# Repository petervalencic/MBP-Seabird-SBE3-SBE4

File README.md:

# Arduino Seabird SBE3 SBE4 

The project contains C/C++ code for Ardiuno Uno and a shield (Eagle project) for SBE-3 and SBE-4 

# SBE 3
Intended primarily for use on moored and fixed-site temperature measuring systems, the SBE 3S can also be used as a component in custom systems or for high-accuracy industrial and environmental temperature monitoring applications. The low noise characteristics of the SBE 3S allow the use of hybrid frequency measuring techniques to obtain rapid sampling with very high resolution; 40 μ°C resolution can be readily obtained at a 6 Hz sampling rate.

CALIBRATION EQUATION

The calibration yields four coefficients (g, h, i, j) that are used in the following equation (Bennett, 1972):

T [°C] = [1 / (g + hln(fo/f) + iln²(fo/f) + jln³(fo/f) )] - 273.15

where T is temperature [°C], ln is natural log function, and f is SBE 3S output frequency [Hz]. Note that fo, an arbitrary scaling term used for purposes of computational efficiency, was historically chosen as the lowest sensor frequency generated during calibration. For calibration results expressed in terms of ITS-90 temperatures, fo is set to 1000. Calibration fit residuals are typically less than 0.0001 °C.

Example Calibration Data (sensor serial number 2213, 30 May 1996):
g = 4.28793855e-03     h = 6.25807786e-04     i = 2.19368239e-05     j = 1.84262924e-06     f0 = 1000.000

# SBE 4
The SBE 4 conductivity sensor is a modular, self-contained instrument that measures conductivity from 0 to 7 S/m, covering the full range of lake and oceanic applications. The sensor has electrically isolated power circuits and optically coupled outputs to eliminate any possibility of noise and corrosion caused by ground loops. Interfacing is also simplified by the square-wave variable frequency output signal (nominally 2.5 to 7.5 kHz, corresponding to 0 to 7 S/m). The sensor offers improved temperature compensation, smaller fit residuals, and faster turn-on stabilization times.

Because of the SBE 4’s low noise characteristics, hybrid frequency measuring techniques (used in Sea-Bird’s CTD instruments) provide rapid sampling with very high temporal and spatial resolution.

CALIBRATION EQUATION

A least-squares fitting technique (including a zero conductivity point in air) yields calibration coefficients for use in the following equation:

Conductivity [S/m] = ( g + hf 2 + if 3+ jf 4 ) / 10 (1 + dt + ep)

where f is instrument frequency [kHz], t is temperature [°C], p is pressure [decibars], and d is thermal coefficient of expansion (3.25 x 10 -06) and e is bulk compressibility (-9.57 x 10 -08) of the borosilicate cell. The resulting coefficients g, h, i, and j are listed on the calibration certificate. Residuals are typically less than 0.0002 S/m.

Example Calibration Data (sensor serial number 2020, 30 May 1997)

Practical Salinity Scale 1978: C(35,15,0) = 4.2914 [S/m]

g = -1.05697877e+01    h = 1.42707291e+00    i = -4.32023820e-03    j = 4.53455585e-04

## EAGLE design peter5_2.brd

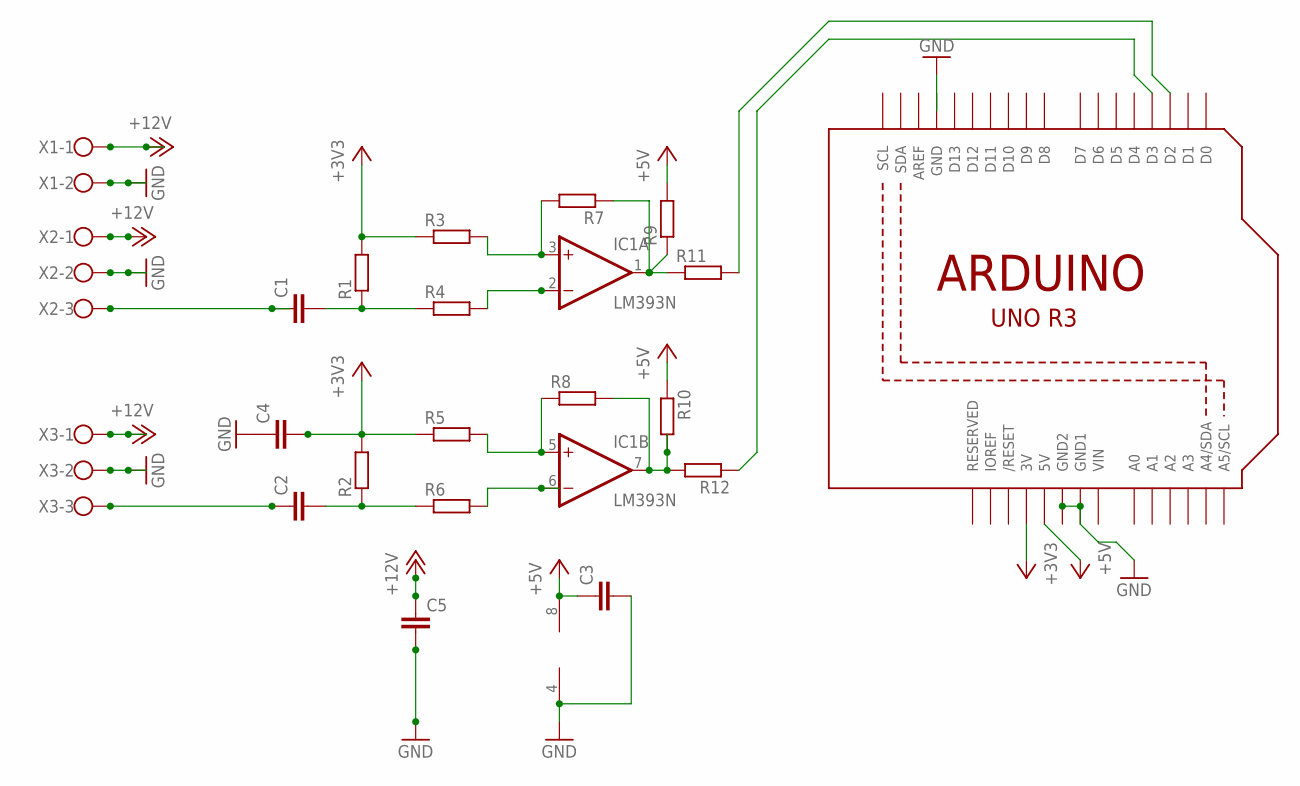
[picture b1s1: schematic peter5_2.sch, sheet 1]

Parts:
C1, C2, C3, C4: C-EU025-040X050; C025-040X050
C5: C2.5/2; C2.5-2
IC1: LM393N; DIL08; MPN LM393N...
R1, R2, R3, R4, R5, R6, R7, R8, R9, R10, R11, R12: R-EU_0207/7; 0207/7
U1: ARDUINOR3-BPLACE
X1: W237-102
X2, X3: W237-103

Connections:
+3V3: C4.2, R1.2, R2.2, R3.1, R5.1, U1.3V
+5V: C3.1, IC1.8 (V+), R9.2, R10.1, U1.5V
+12V: C5.1, X1.1, X2.1, X3.1
GND: C3.2, C4.1, C5.2, IC1.4 (V-), U1.GND, X1.2, X2.2, X3.2
GND1: U1.GND1
GND2: U1.GND2
unnamed: IC1.3 (+IN), R3.2, R7.2
unnamed: IC1.2 (-IN), R4.2
unnamed: IC1.1 (OUT), R7.1, R9.1, R11.1
unnamed: R11.2, U1.D2
unnamed: R12.1, U1.D3
unnamed: C1.2, R1.1, R4.1
unnamed: IC1.7 (OUT), R8.2, R10.2, R12.2
unnamed: C2.1, X3.3
unnamed: IC1.5 (+IN), R5.2, R8.1
unnamed: IC1.6 (-IN), R6.2
unnamed: C2.2, R2.1, R6.1
unnamed: C1.1, X2.3
VIN: U1.VIN

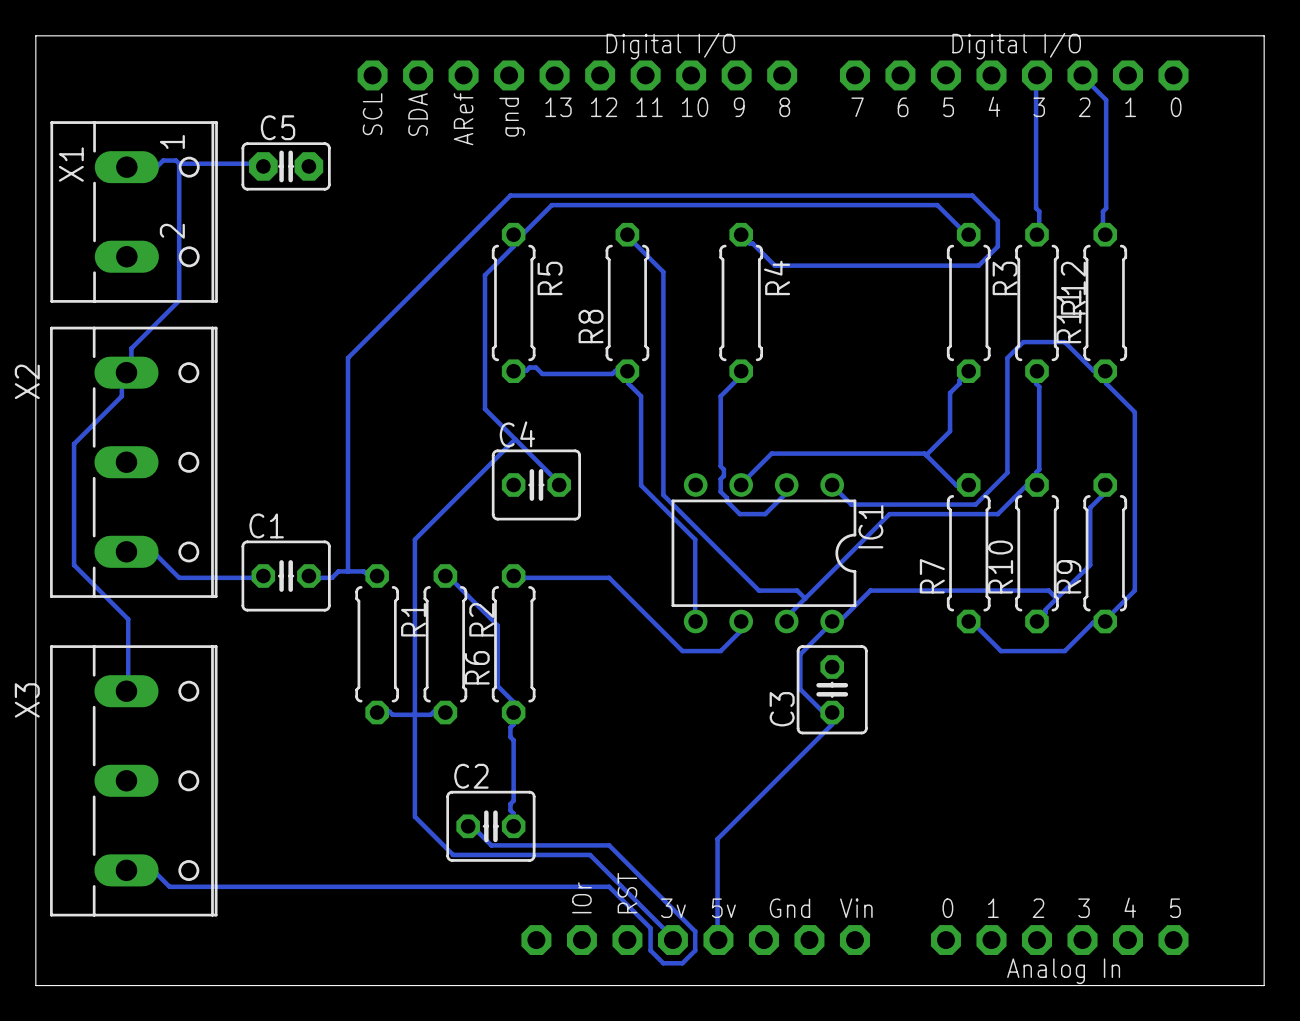
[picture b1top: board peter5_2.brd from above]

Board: 2 copper layers, 68.6 x 53.0 mm, 22 parts (0 on the bottom side), 16 nets.

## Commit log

2017-10-18 Create network.txt
    Network configuration file.
    This file is stored on SD card which is then inserted into Arduino network/SD shield.
    The file contains
    MAC adress
    IP adress
    NetMask
2017-10-19 Create Shield
2017-10-19 Create bb
2017-12-10 Update maincode.ino
    Dodano preračunavanje slanosti
2017-12-10 Update maincode.ino
    Dodano pošiljanje XML-a
2017-12-18 Update maincode.ino
    - preračun slanosti se vrši KHz!
2018-04-15 Create ConductivitySalinity.java
    Simple testing script for conductivity and salinity
2018-08-10 Update maincode.ino
    spremenjeni nazivi spremenljivk
2018-08-12 Update maincode.ino
    - optimizacija določenih stringov in izpisov
